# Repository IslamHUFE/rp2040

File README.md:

# RP2040 DevKit

A custom development board built around the **Raspberry Pi RP2040** microcontroller.

This project is a personal PCB design exercise based on the official RP2040 hardware-design reference material. The goal was to translate the reference design into a complete, organized KiCad project and develop a practical DevKit-style board around the RP2040.

> **Project status:** PCB design / hardware development

## Overview

The board was designed from the RP2040 reference design with attention to the complete hardware implementation rather than treating the microcontroller as a standalone component. The repository contains the KiCad schematic and PCB layout, supporting component data, manufacturing-related outputs, and visualizations of the finished board.

The design includes the supporting circuitry required around the RP2040, including its clocking and other core hardware, while keeping the board in a compact development-kit form suitable for experimentation and further firmware development.

## Design Files

The main hardware design is provided as a **KiCad project**:

- `RS/RS.kicad_sch` — Schematic
- `RS/RS.kicad_pcb` — PCB layout
- `RS/RS.kicad_pro` — KiCad project file
- `RS/RS.pdf` — Schematic/documentation export
- `RS/bom/` — Bill of Materials and related outputs
- `RS/hi.pretty/` — Custom KiCad footprints used by the project
- `3D/` — Additional 3D component model files
- `ref/` — Reference material used during the design process

## PCB Layer Stack

The following renders show the PCB layer-by-layer, followed by a combined view of the complete board stack.

### Layer 1 — Top Layer

The first layer of the PCB, showing the routing and copper features placed on the top side of the board.

### Layer 2 — Inner Layer

The second PCB layer, showing the corresponding internal copper features and routing.

### Layer 3 — Inner Layer

The third layer of the four-layer PCB stack, providing additional routing and copper area within the board.

### Layer 4 — Bottom Layer

The final layer of the PCB stack, showing the copper features on the bottom side of the board.

### Complete Layer Stack

All four PCB layers displayed together to give an overall view of the board's routing density and layer organization.

## 3D PCB Views

The following renders show the completed PCB from different perspectives. They provide a more intuitive view of the board outline, component placement, connectors, and overall physical arrangement.

### 3D View — Front Perspective

A perspective view of the assembled PCB, highlighting the component placement and overall board geometry.

### 3D View — Alternate Perspective

A second perspective of the board showing the physical arrangement from a different angle.

### 3D View — Final Overview

A final 3D overview of the DevKit, showing the complete board design as a physical assembly.

## Design Process

The board was developed by studying the RP2040 hardware reference design and adapting its requirements into a custom PCB workflow:

1. **Reference study** — Understanding the RP2040's required supporting circuitry and hardware constraints.
2. **Schematic design** — Recreating and organizing the required circuitry in KiCad.
3. **Component and footprint selection** — Selecting appropriate packages and creating or integrating required footprints and 3D models.
4. **PCB layout** — Arranging the circuitry and routing the board across the four-layer stackup.
5. **Design review** — Inspecting the individual PCB layers and the complete layout.
6. **3D verification** — Using KiCad's 3D representation to check the physical arrangement and board geometry.

## Reference

The design was developed with the **RP2040 hardware design documentation** as a primary reference. The relevant reference material is included in the [`ref/`](ref/) directory for reproducibility and study.

## Tools

- **KiCad 10** — Schematic capture, PCB layout, and 3D inspection
- **RP2040** — Main microcontroller
- **Git / GitHub** — Version control and project documentation

## Notes

This repository represents a custom hardware implementation and learning project. It is based on the RP2040 reference design, but the PCB, schematic organization, component selection, and physical layout were developed as part of this project.

The design should be reviewed and electrically validated before being used as a production board.

---

**Designed by Islam Tarek Moawad**

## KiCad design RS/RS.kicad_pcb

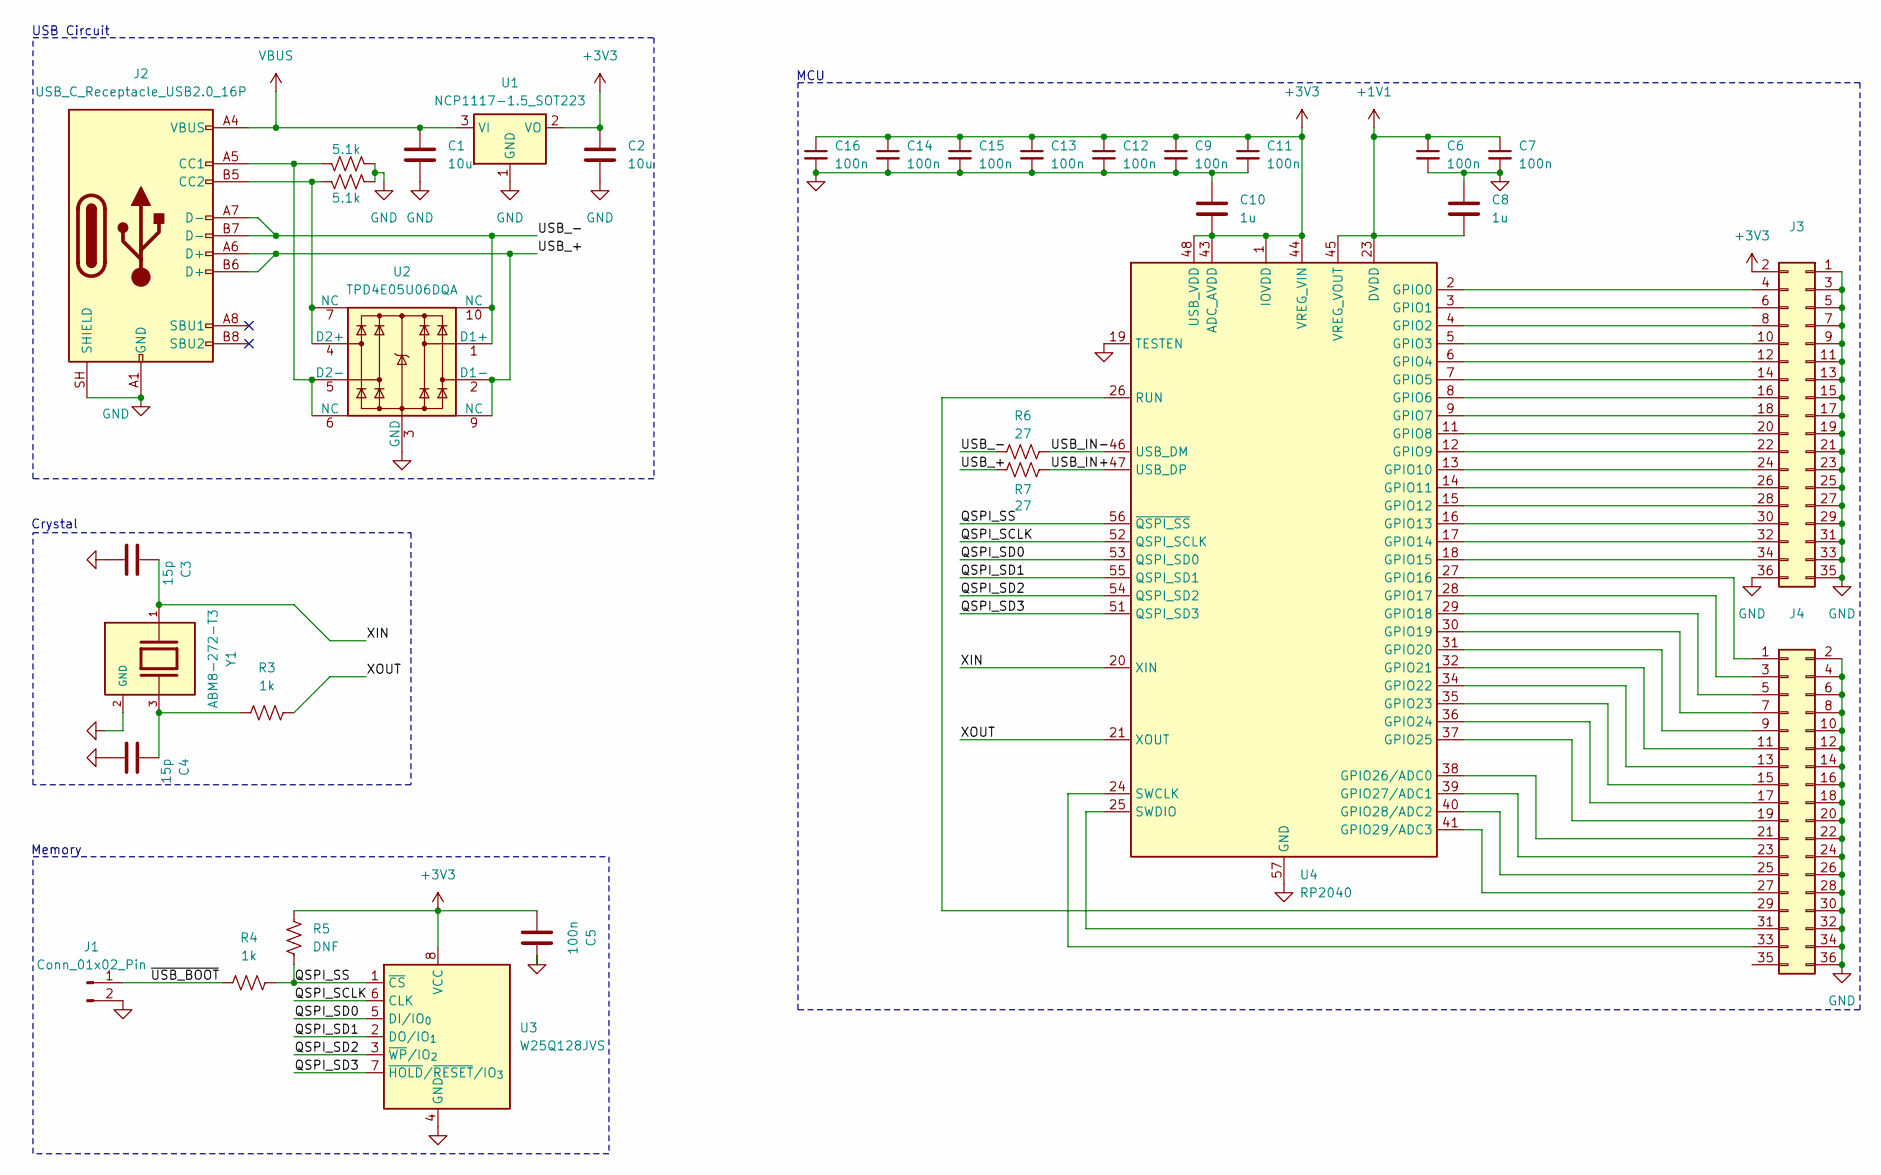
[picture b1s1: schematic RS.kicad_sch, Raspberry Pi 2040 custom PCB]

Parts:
C1, C2: 10u; C_0805_2012Metric
C3, C4: 15p; C_01005_0402Metric
C5: 100n; C_01005_0402Metric
C6, C7, C9, C11, C12, C13, C14, C15, C16: 100n; C_0402_1005Metric
C8, C10: 1u; C_0805_2012Metric
J1: Conn_01x02_Pin; PinHeader_1x02_P1.00mm_Vertical
J2: USB_C_Receptacle_USB2.0_16P; USB_C_Receptacle_GCT_USB4105-xx-A_16P_TopMnt_Horizontal
J3, J4: Conn_02x18_Odd_Even; PinHeader_2x18_P2.54mm_Vertical
R1, R2: 5.1k; R_0402_1005Metric
R3, R4: 1k; R_0402_1005Metric
R5: DNF; R_0402_1005Metric
R6, R7: 27; R_0402_1005Metric
U1: NCP1117-1.5_SOT223; SOT-223-3_TabPin2
U2: TPD4E05U06DQA; USON-10_2.5x1.0mm_P0.5mm
U3: W25Q128JVS; SOIC-8_5.3x5.3mm_P1.27mm
U4: RP2040; QFN-56-1EP_7x7mm_P0.4mm_EP3.2x3.2mm
Y1: ABM8-272-T3; Crystal_SMD_Abracon_ABM8G-4Pin_3.2x2.5mm; PARTREV 07-29-20

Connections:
+1V1: C6.1, C7.1, C8.2, U4.23 (DVDD), U4.45 (VREG_VOUT), U4.50 (DVDD)
+3V3: C2.1, C5.1, C9.1, C10.2, C11.1, C12.1, C13.1, C14.1, C15.1, C16.1, J3.2, R5.2, U1.2 (VO), U3.8 (VCC), U4.1 (IOVDD), U4.10 (IOVDD), U4.22 (IOVDD), U4.33 (IOVDD), U4.42 (IOVDD), U4.43 (ADC_AVDD), U4.44 (VREG_VIN), U4.48 (USB_VDD), U4.49 (IOVDD)
/QSPI_SCLK: U3.6 (CLK), U4.52 (QSPI_SCLK)
/QSPI_SD0: U3.5 (DI/IO_{0}), U4.53 (QSPI_SD0)
/QSPI_SD1: U3.2 (DO/IO_{1}), U4.55 (QSPI_SD1)
/QSPI_SD2: U3.3 (~WP/IO_{2}), U4.54 (QSPI_SD2)
/QSPI_SD3: U3.7 (~HOLD/~RESET/IO_{3}), U4.51 (QSPI_SD3)
/QSPI_SS: R4.2, R5.1, U3.1 (~CS), U4.56 (~QSPI_SS)
/USB_+: J2.A6 (D+), J2.B6 (D+), R7.1, U2.2 (D1-), U2.9 (NC)
/USB_-: J2.A7 (D-), J2.B7 (D-), R6.1, U2.1 (D1+), U2.10 (NC)
/USB_IN+: R7.2, U4.47 (USB_DP)
/USB_IN-: R6.2, U4.46 (USB_DM)
/XIN: C3.1, U4.20 (XIN), Y1.1
/XOUT: R3.2, U4.21 (XOUT)
/~USB_BOOT: J1.1, R4.1
GND: C1.2, C2.2, C3.2, C4.2, C5.2, C6.2, C7.2, C8.1, C9.2, C10.1, C11.2, C12.2, C13.2, C14.2, C15.2, C16.2, J1.2, J2.A1 (GND), J2.A12 (GND), J2.B1 (GND), J2.B12 (GND), J2.SH (SHIELD), J3.1, J3.3, J3.5, J3.7, J3.9, J3.11, J3.13, J3.15, J3.17, J3.19, J3.21, J3.23, J3.25, J3.27, J3.29, J3.31, J3.33, J3.35, J3.36, J4.2, J4.4, J4.6, J4.8, J4.10, J4.12, J4.14, J4.16, J4.18, J4.20, J4.22, J4.24, J4.26, J4.28, J4.30, J4.32, J4.34, J4.36, R1.1, R2.1, U1.1 (GND), U2.3 (GND), U2.8 (GND), U3.4 (GND), U4.19 (TESTEN), U4.57 (GND), Y1.2 (GND), Y1.4 (GND)
unnamed: C4.1, R3.1, Y1.3
unnamed: J2.A5 (CC1), R2.2, U2.5 (D2-), U2.6 (NC)
unnamed: J2.B5 (CC2), R1.2, U2.4 (D2+), U2.7 (NC)
unnamed: J3.4, U4.2 (GPIO0)
unnamed: J3.6, U4.3 (GPIO1)
unnamed: J3.8, U4.4 (GPIO2)
unnamed: J3.10, U4.5 (GPIO3)
unnamed: J3.12, U4.6 (GPIO4)
unnamed: J3.14, U4.7 (GPIO5)
unnamed: J3.16, U4.8 (GPIO6)
unnamed: J3.18, U4.9 (GPIO7)
unnamed: J3.20, U4.11 (GPIO8)
unnamed: J3.22, U4.12 (GPIO9)
unnamed: J3.24, U4.13 (GPIO10)
unnamed: J3.26, U4.14 (GPIO11)
unnamed: J3.28, U4.15 (GPIO12)
unnamed: J3.30, U4.16 (GPIO13)
unnamed: J3.32, U4.17 (GPIO14)
unnamed: J3.34, U4.18 (GPIO15)
unnamed: J4.1, U4.27 (GPIO16)
unnamed: J4.3, U4.28 (GPIO17)
unnamed: J4.5, U4.29 (GPIO18)
unnamed: J4.7, U4.30 (GPIO19)
unnamed: J4.9, U4.31 (GPIO20)
unnamed: J4.11, U4.32 (GPIO21)
unnamed: J4.13, U4.34 (GPIO22)
unnamed: J4.15, U4.35 (GPIO23)
unnamed: J4.17, U4.36 (GPIO24)
unnamed: J4.19, U4.37 (GPIO25)
unnamed: J4.21, U4.38 (GPIO26/ADC0)
unnamed: J4.23, U4.39 (GPIO27/ADC1)
unnamed: J4.25, U4.40 (GPIO28/ADC2)
unnamed: J4.27, U4.41 (GPIO29/ADC3)
unnamed: J4.29, U4.26 (RUN)
unnamed: J4.31, U4.25 (SWDIO)
unnamed: J4.33, U4.24 (SWCLK)
VBUS: C1.1, J2.A4 (VBUS), J2.A9 (VBUS), J2.B4 (VBUS), J2.B9 (VBUS), U1.3 (VI)

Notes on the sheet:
Crystal
USB Circuit
Memory
MCU

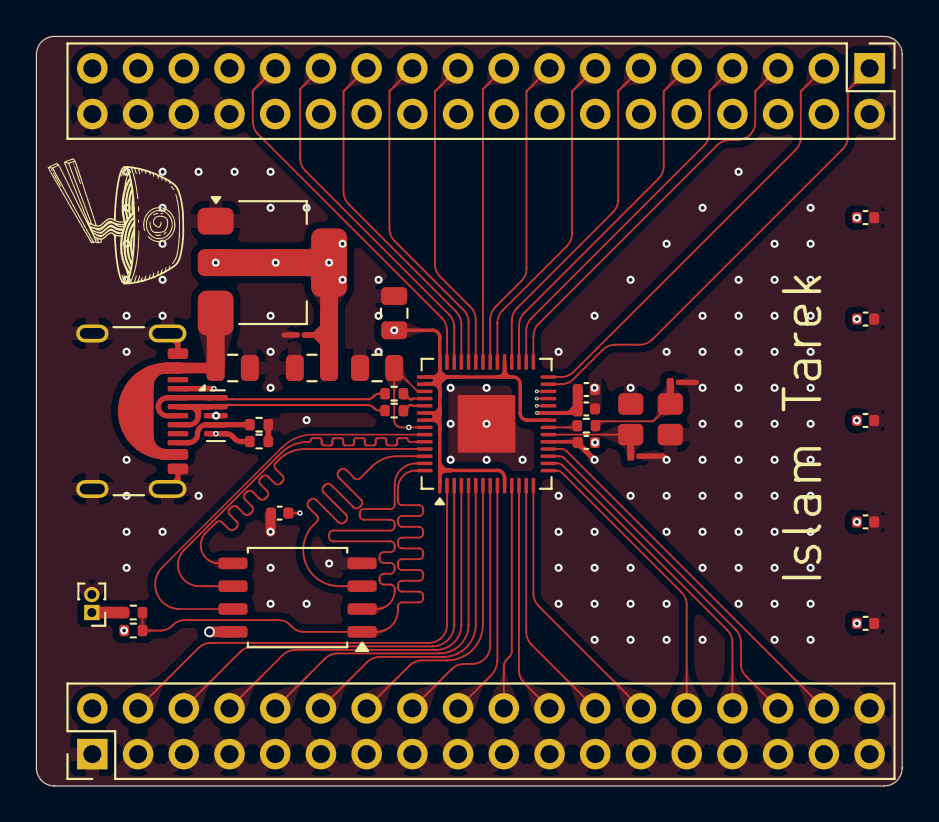
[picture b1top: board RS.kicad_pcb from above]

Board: 4 copper layers, 48.1 x 41.6 mm, 32 parts (0 on the bottom side), 53 nets.
